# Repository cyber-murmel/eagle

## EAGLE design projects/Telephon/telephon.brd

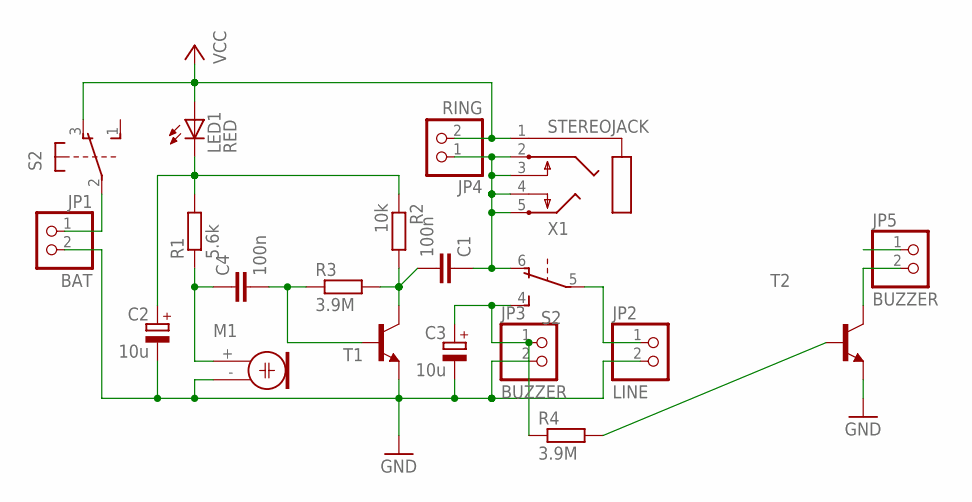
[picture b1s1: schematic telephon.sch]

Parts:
C1, C4: 100n; C025-025X050
C2, C3: 10u; B45181A
JP1: BAT; 1X02
JP2: LINE; 1X02
JP3, JP5: BUZZER; 1X02
JP4: RING; 1X02
LED1: RED; LED5MM
M1: ELECTRET; 9.7ELECTRET
R1: 5.6k; 0204/7
R2: 10k; 0204/7
R3, R4: 3.9M; 0204/7
S2: 9450-2
T1, T2: BC547-NPN-TO92-CBE; TO92-CBE
X1: STEREOJACK; STX3100

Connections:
GND: C2.-, C3.-, JP1.2, JP2.2, JP3.2, M1.- (1), T1.E, T2.E
unnamed: C3.+, JP3.1, R4.1, S2.4 (S)
unnamed: JP5.2, T2.C
unnamed: R4.2, T2.B
unnamed: C4.2, R3.1, T1.B
unnamed: C4.1, M1.+ (2), R1.1
unnamed: C1.2, R2.2, R3.2, T1.C
unnamed: C1.1, JP4.1, S2.6 (O), X1.2, X1.3, X1.4, X1.5
unnamed: C2.+, LED1.K (C), R1.2, R2.1
unnamed: JP2.1, S2.5
unnamed: JP1.1, S2.2
VCC: JP4.2, LED1.A, S2.3 (O), X1.1

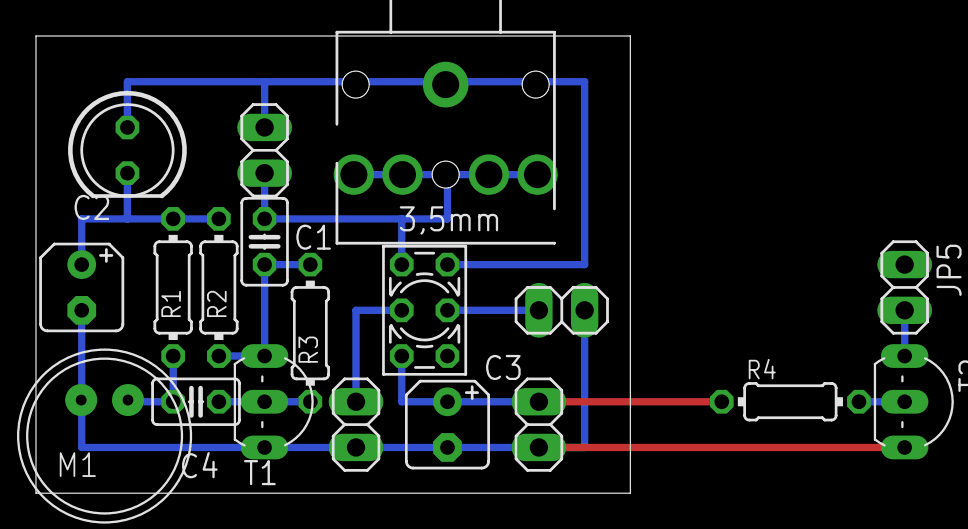
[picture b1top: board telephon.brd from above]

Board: 2 copper layers, 33.0 x 25.4 mm, 19 parts (0 on the bottom side), 12 nets.

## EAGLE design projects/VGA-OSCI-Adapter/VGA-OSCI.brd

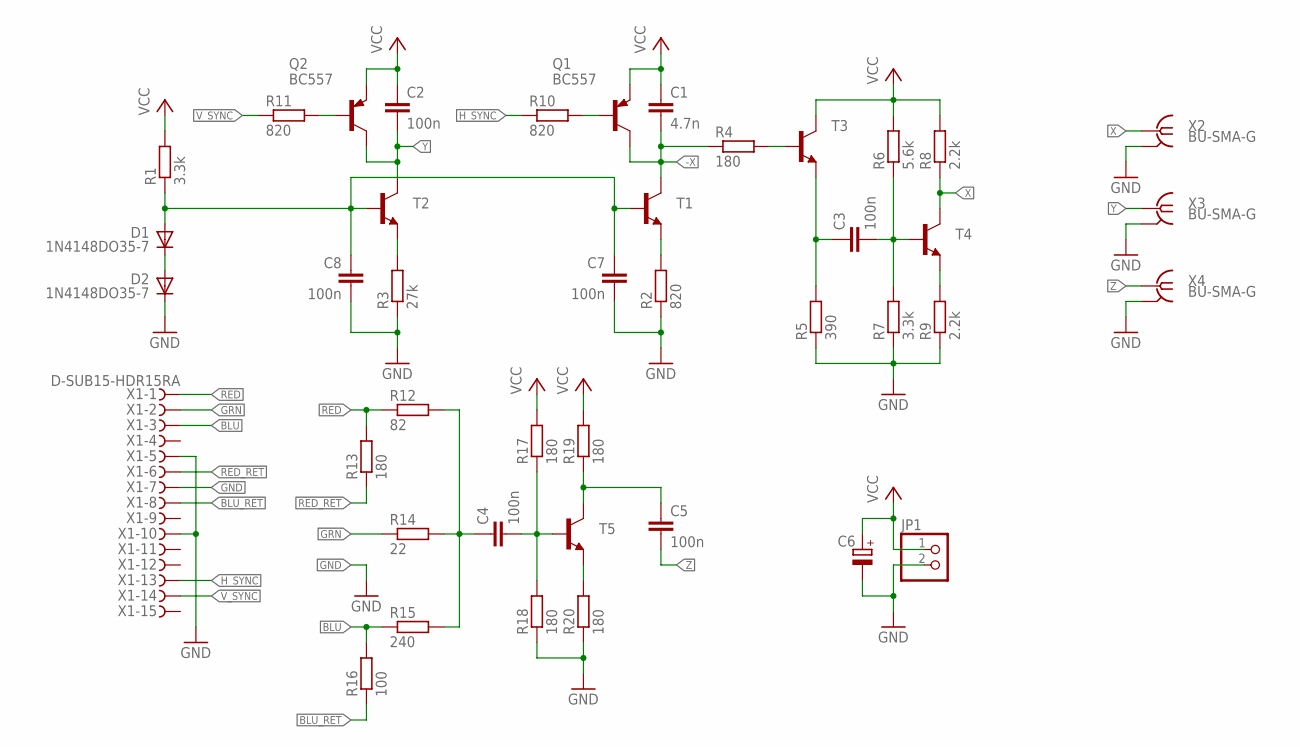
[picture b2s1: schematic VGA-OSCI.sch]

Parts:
C1: 4.7n; C050-024X044
C2, C3, C4, C5, C7, C8: 100n; C050-024X044
C6: CPOL-EUB45181A; B45181A
D1, D2: 1N4148DO35-7; DO35-7
JP1: PINHD-1X2; 1X02
Q1, Q2: BC557; TO92-EBC
R1, R7: 3.3k; 0204/7
R2, R10, R11: 820; 0204/7
R3: 27k; 0204/7
R4, R13, R17, R18, R19, R20: 180; 0204/7
R5: 390; 0204/7
R6: 5.6k; 0204/7
R8, R9: 2.2k; 0204/7
R12: 82; 0204/7
R14: 22; 0204/7
R15: 240; 0204/7
R16: 100; 0204/7
T1, T2, T3, T4, T5: BC547-NPN-TO92-CBE; TO92-CBE
X1: D-SUB15-HDR15RA; HDR15RA
X2, X3, X4: BU-SMA-G

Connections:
-X: C1.2, Q1.C, R4.1, T1.C
BLU: R15.1, R16.2, X1.3
BLU_RET: R16.1, X1.8
GND: C6.-, C7.2, C8.2, D2.C, JP1.2, R2.1, R3.1, R5.1, R7.1, R9.1, R18.1, R20.1, X1.5, X1.7, X1.10, X2.2, X2.3 (2), X2.4 (2), X2.5 (2), X3.2, X3.3 (2), X3.4 (2), X3.5 (2), X4.2, X4.3 (2), X4.4 (2), X4.5 (2)
GRN: R14.1, X1.2
GRY_SCL: C4.1, R12.2, R14.2, R15.2
H_SYNC: R10.1, X1.13
unnamed: D1.C, D2.A
unnamed: C7.1, C8.1, D1.A, R1.1, T1.B, T2.B
unnamed: R2.2, T1.E
unnamed: R3.2, T2.E
unnamed: Q2.B, R11.2
unnamed: R9.2, T4.E
unnamed: C3.2, R6.1, R7.2, T4.B
unnamed: C3.1, R5.2, T3.E
unnamed: R4.2, T3.B
unnamed: Q1.B, R10.2
unnamed: C4.2, R17.1, R18.2, T5.B
unnamed: C5.1, R19.1, T5.C
unnamed: R20.2, T5.E
RED: R12.1, R13.2, X1.1
RED_RET: R13.1, X1.6
VCC: C1.1, C2.1, C6.+, JP1.1, Q1.E, Q2.E, R1.2, R6.2, R8.2, R17.2, R19.2, T3.C
V_SYNC: R11.1, X1.14
X: R8.1, T4.C, X2.1
Y: C2.2, Q2.C, T2.C, X3.1
Z: C5.2, X4.1

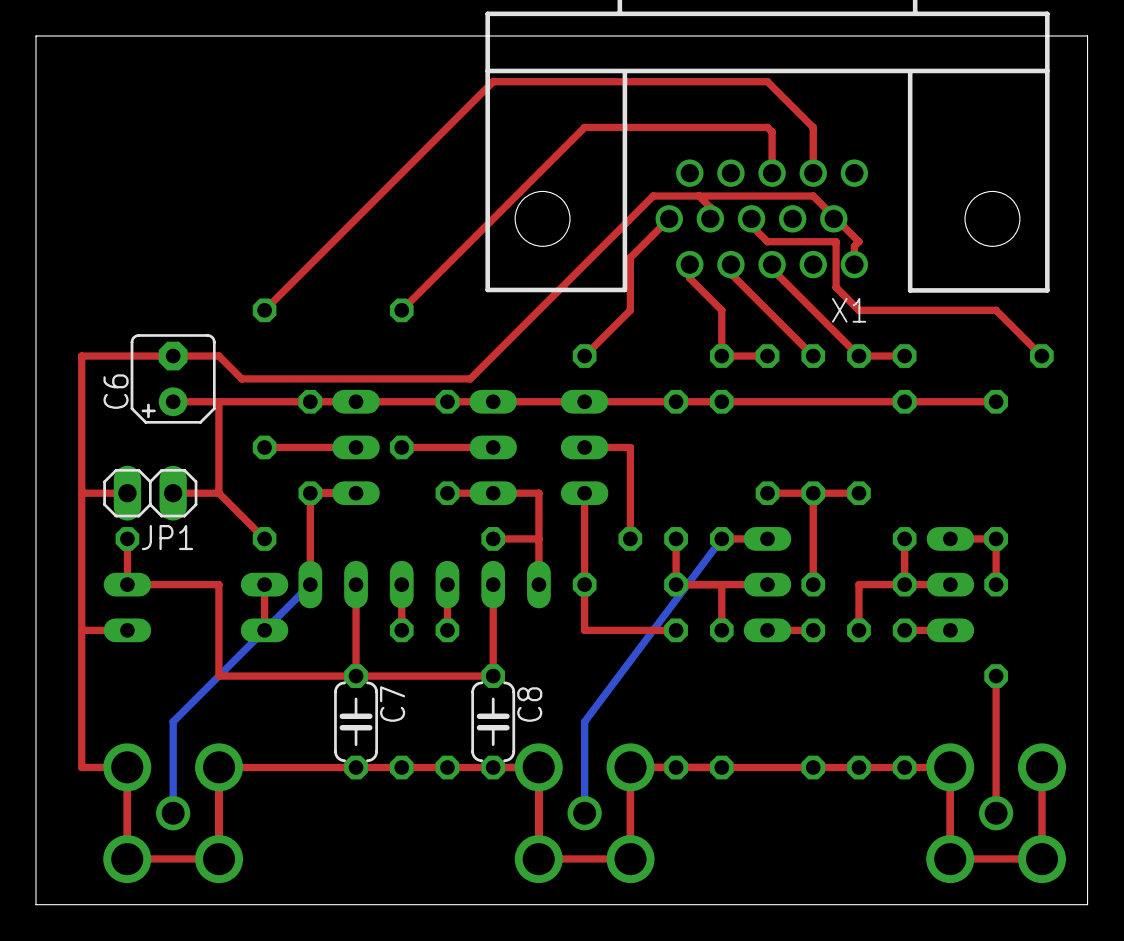
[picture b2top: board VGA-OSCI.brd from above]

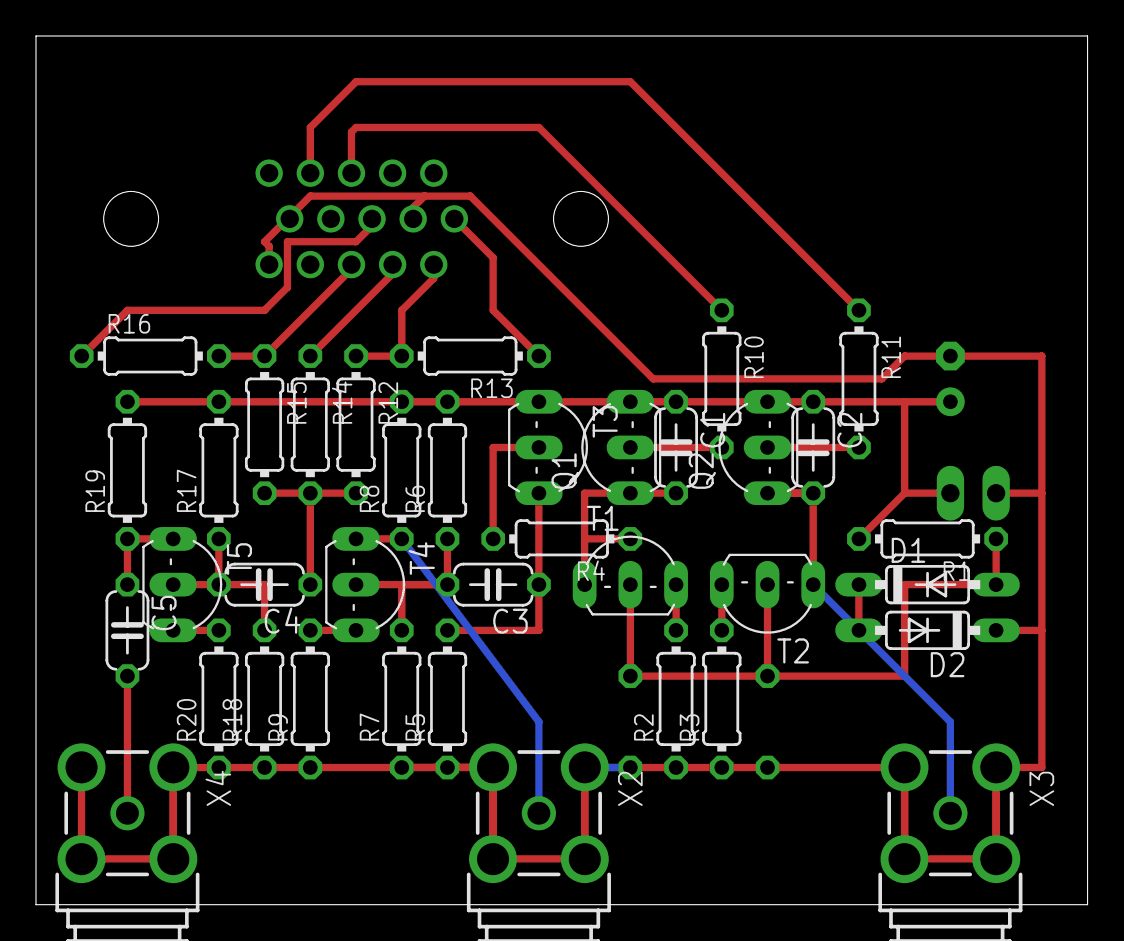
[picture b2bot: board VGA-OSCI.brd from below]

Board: 2 copper layers, 58.4 x 48.3 mm, 42 parts (37 on the bottom side), 27 nets.

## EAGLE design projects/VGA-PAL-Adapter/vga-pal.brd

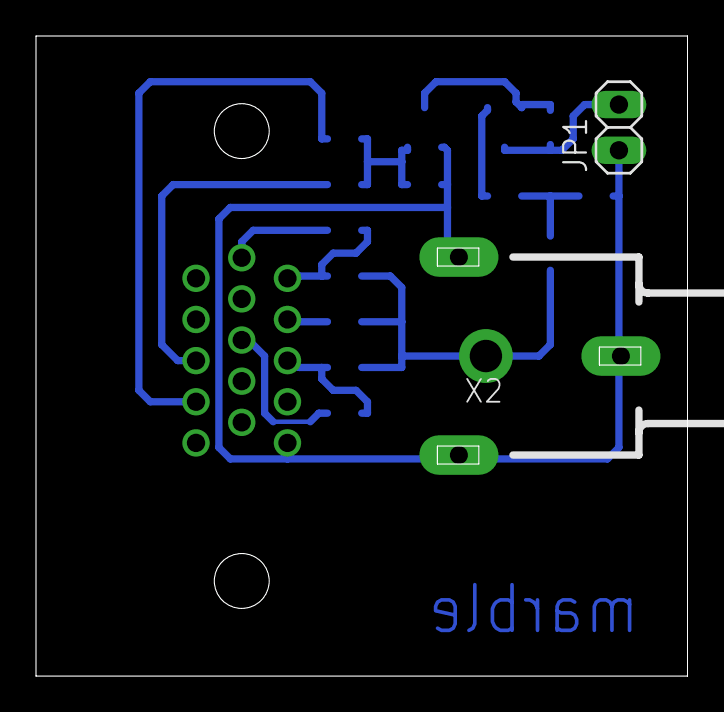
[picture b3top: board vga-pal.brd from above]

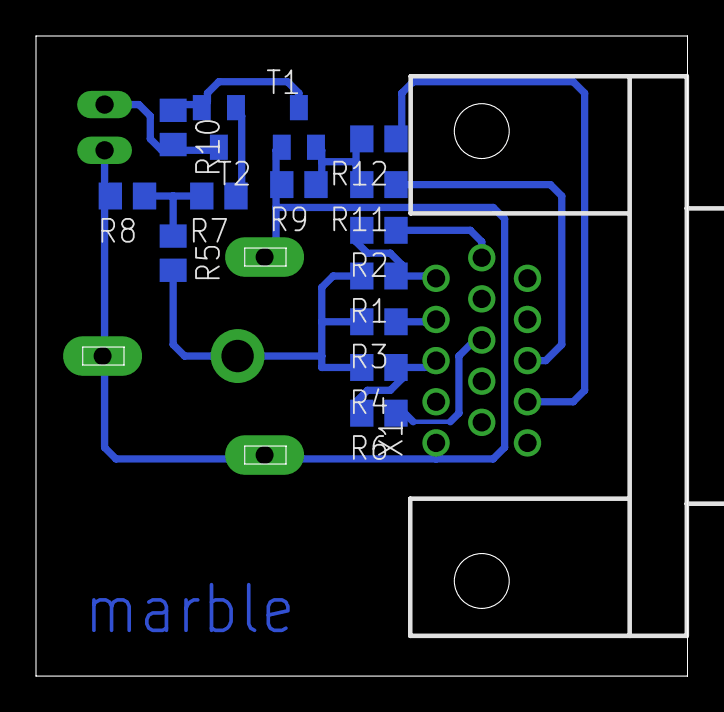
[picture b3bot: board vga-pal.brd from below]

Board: 2 copper layers, 36.2 x 35.6 mm, 17 parts (15 on the bottom side), 14 nets.

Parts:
JP1: PSU; 1X02
R1: 82; R0805
R2: 180; R0805
R3: 22; R0805
R4: 220; R0805
R5, R6: 100; R0805
R7, R8: 68; R0805
R9, R11, R12: 1.8k; R0805
R10: 2.7k; R0805
T1, T2: SOT23-EBC
X1: D-SUB15-HDR15RA; HDR15RA
X2: 736880-49

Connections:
BLU: R4.1, R6.2, X1.3
BLU_GND: R6.1, X1.8
GND: JP1.1, R8.2, R9.2, T1.E, X1.5, X2.1, X2.1@1, X2.1@2
GRN: R3.1, X1.2
H_SYNC: R11.1, X1.13
unnamed: R1.2, R3.2, R4.2, R5.2, X2.2
unnamed: R5.1, R7.2, R8.1
unnamed: R9.1, R11.2, R12.2, T1.B
unnamed: R10.1, T1.C, T2.B
unnamed: R7.1, T2.E
RED: R1.1, R2.2, X1.1
R_GND: R2.1, X1.6
VCC: JP1.2, R10.2, T2.C
V_SYNC: R12.1, X1.14

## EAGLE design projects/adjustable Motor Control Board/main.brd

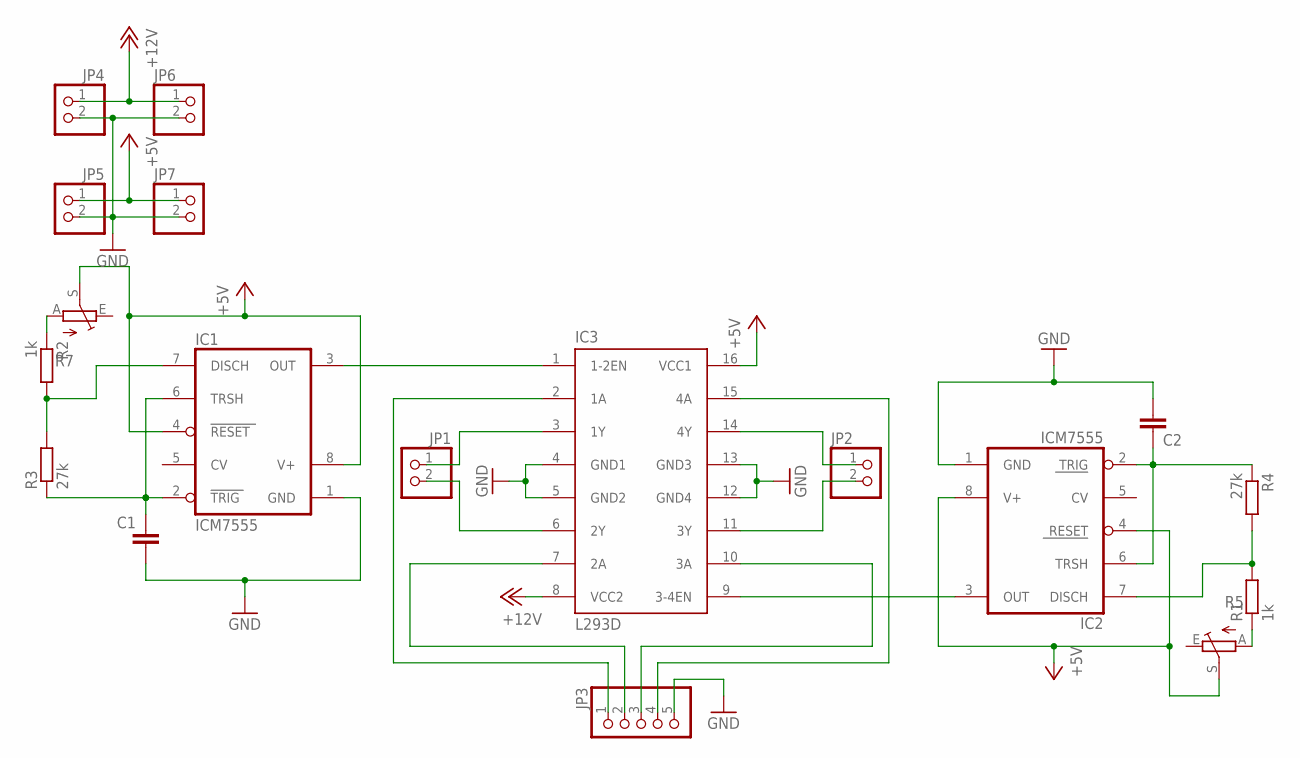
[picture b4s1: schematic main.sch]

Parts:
C1, C2: C-EU025-025X050; C025-025X050
IC1, IC2: ICM7555; DIL08
IC3: L293D; DIL16
JP1, JP2, JP4, JP5, JP6, JP7: PINHD-1X2; 1X02
JP3: PINHD-1X5; 1X05
R1, R2: 1k; 0204/7
R3, R4: 27k; 0204/7
R5, R7: TRIM_EU-LI15; LI15

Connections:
+5V: IC1.4 (RESET), IC1.8 (V+), IC2.4 (RESET), IC2.8 (V+), IC3.16 (VCC1), JP5.1, JP7.1, R5.S, R7.S
+12V: IC3.8 (VCC2), JP4.1, JP6.1
GND: C1.2, C2.2, IC1.1 (GND), IC2.1 (GND), IC3.4 (GND1), IC3.5 (GND2), IC3.12 (GND4), IC3.13 (GND3), JP3.5, JP4.2, JP5.2, JP6.2, JP7.2
unnamed: IC3.15 (4A), JP3.4
unnamed: IC3.3 (1Y), JP1.1
unnamed: IC3.6 (2Y), JP1.2
unnamed: IC3.11 (3Y), JP2.2
unnamed: IC3.14 (4Y), JP2.1
unnamed: IC3.2 (1A), JP3.1
unnamed: IC3.7 (2A), JP3.2
unnamed: IC3.10 (3A), JP3.3
unnamed: C2.1, IC2.2 (TRIG), IC2.6 (TRSH), R4.1
unnamed: C1.1, IC1.2 (TRIG), IC1.6 (TRSH), R3.1
unnamed: IC2.7 (DISCH), R1.2, R4.2
unnamed: R1.1, R5.A
unnamed: IC2.3 (OUT), IC3.9 (3-4EN)
unnamed: IC1.7 (DISCH), R2.2, R3.2
unnamed: IC1.3 (OUT), IC3.1 (1-2EN)
unnamed: R2.1, R7.A

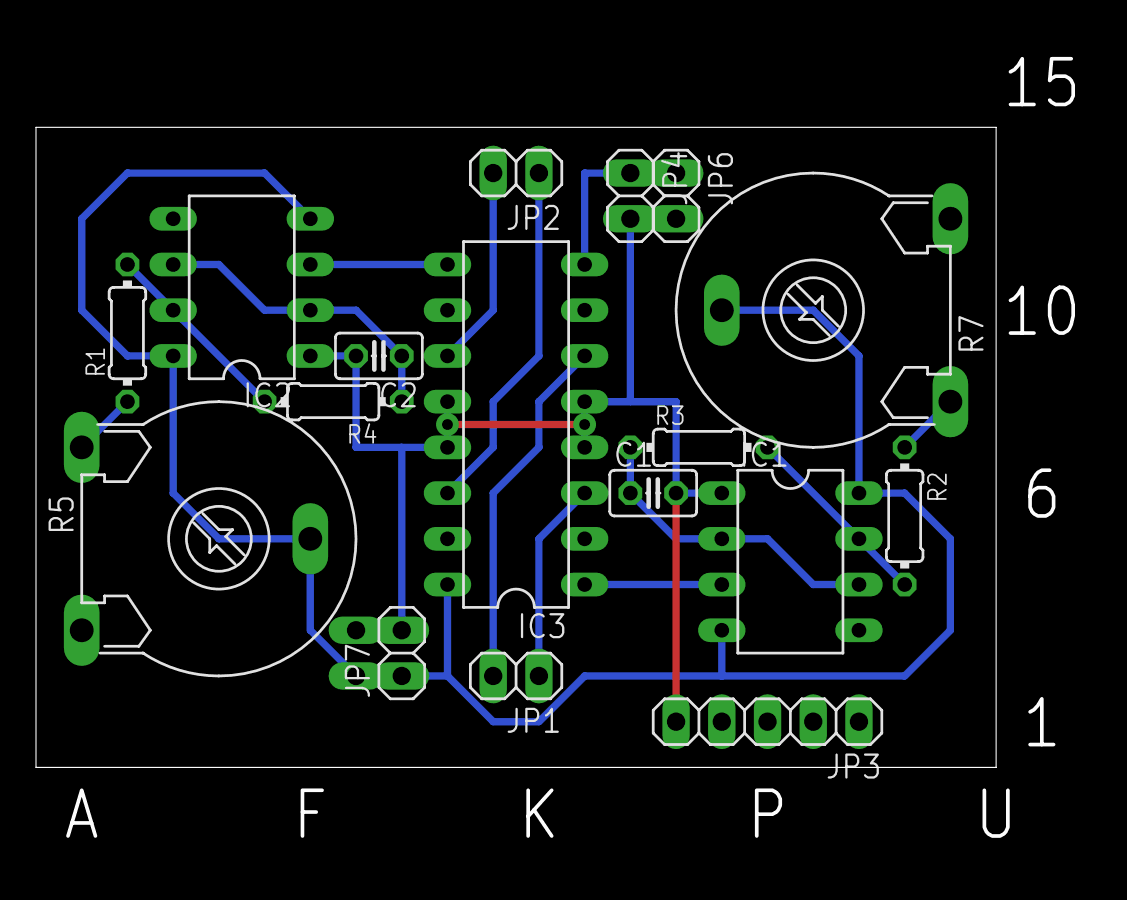
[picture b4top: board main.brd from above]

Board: 2 copper layers, 53.3 x 35.6 mm, 18 parts (1 on the bottom side), 19 nets.

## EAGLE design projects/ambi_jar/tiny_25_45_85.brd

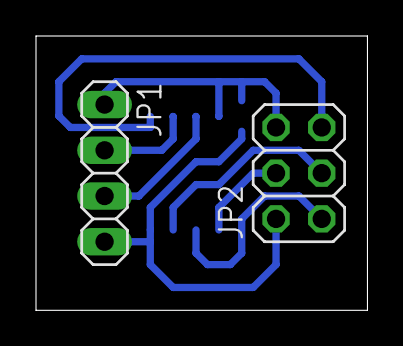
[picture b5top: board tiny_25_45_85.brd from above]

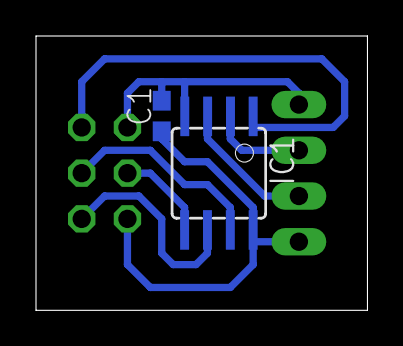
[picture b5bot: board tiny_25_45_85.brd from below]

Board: 2 copper layers, 18.4 x 15.2 mm, 4 parts (2 on the bottom side), 8 nets.

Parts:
C1: C0603
IC1: TINY22S; SOIC8
JP1: 1X04
JP2: 2X03

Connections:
GND: C1.2, IC1.4, JP1.1, JP2.6
unnamed: IC1.3, JP1.3
unnamed: IC1.2, JP1.2
unnamed: IC1.1, JP2.5
unnamed: IC1.5, JP2.4
unnamed: IC1.6, JP2.1
unnamed: IC1.7, JP2.3
VCC: C1.1, IC1.8, JP1.4, JP2.2
